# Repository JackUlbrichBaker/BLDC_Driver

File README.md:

BLDC Driver Board based on the STM32G4 Embedded motor driver:

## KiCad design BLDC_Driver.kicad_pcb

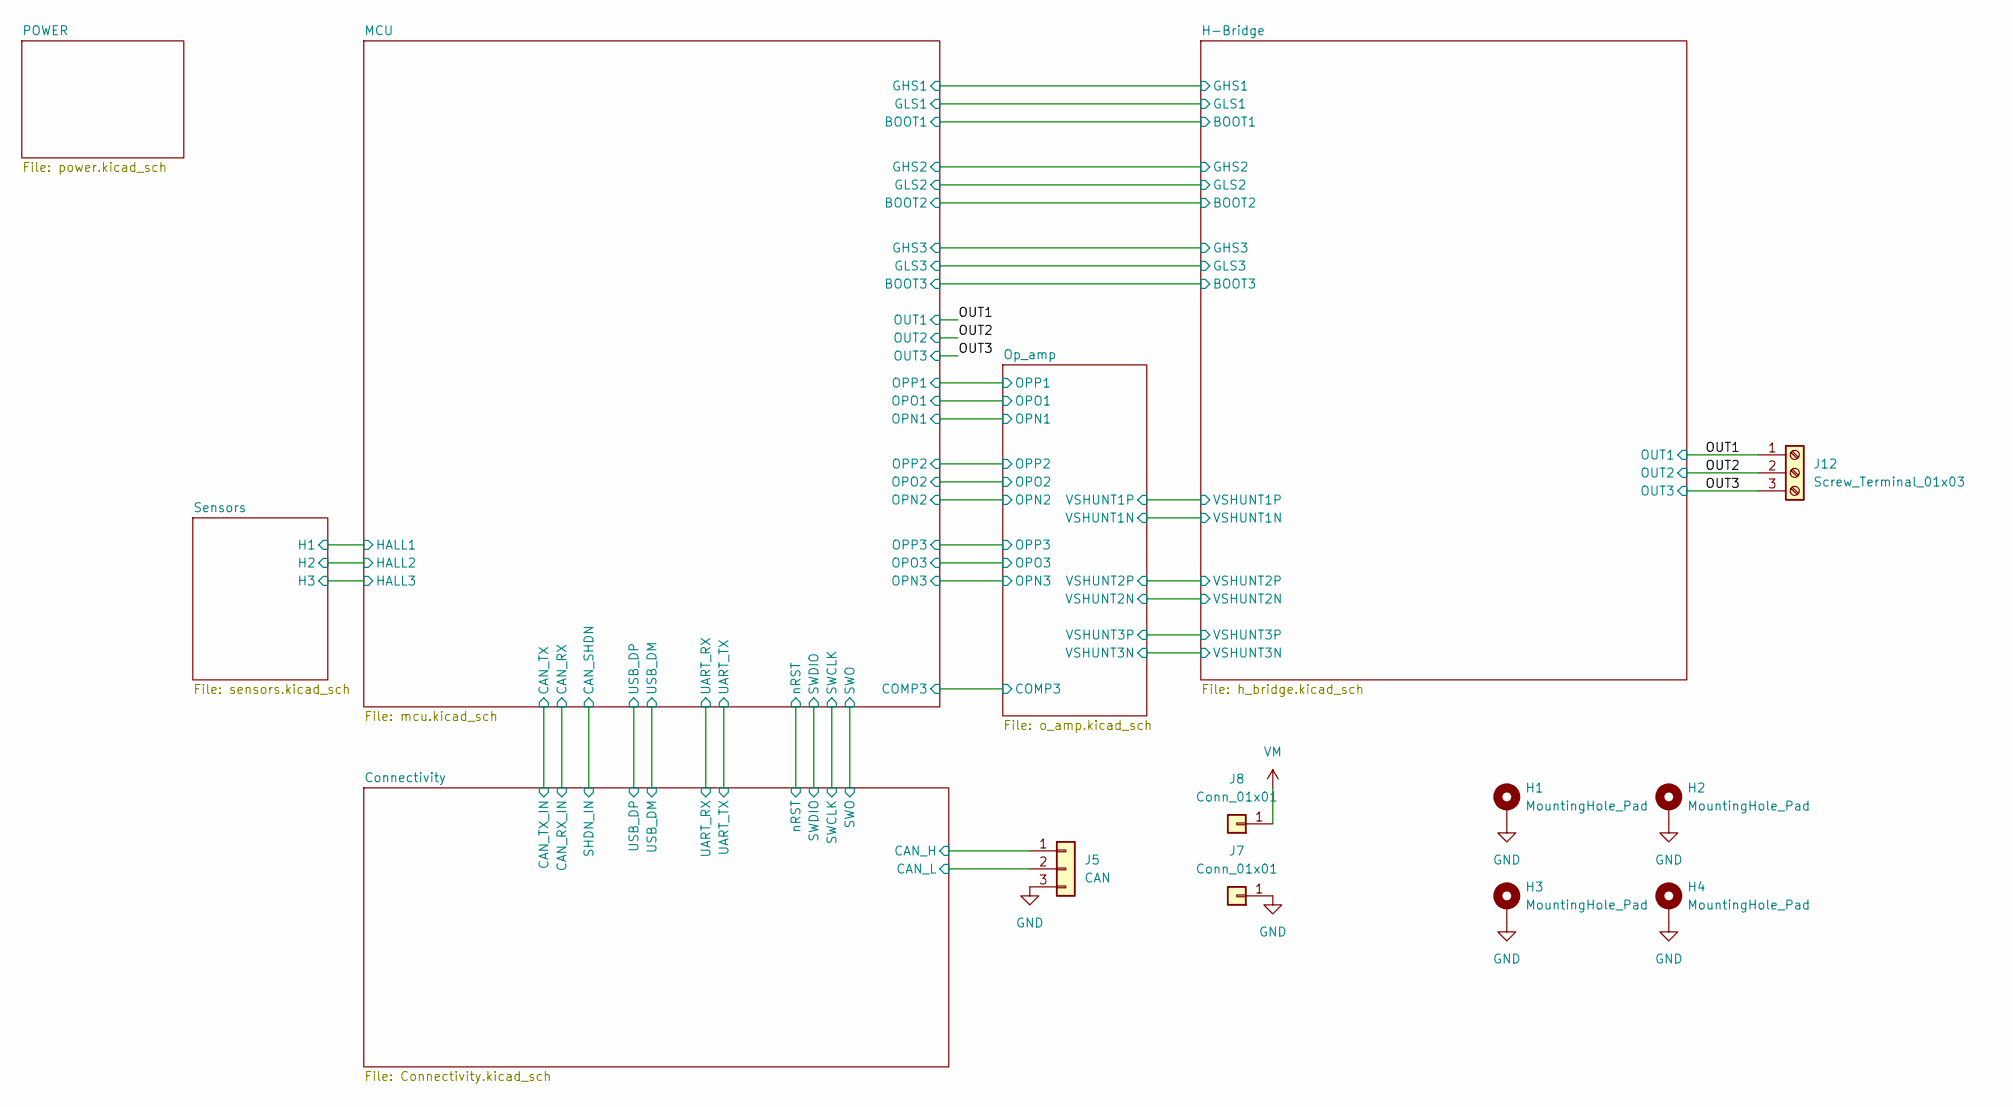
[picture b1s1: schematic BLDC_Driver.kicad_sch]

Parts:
H1, H2, H3, H4: MountingHole_Pad; MountingHole_3.2mm_M3_Pad_Via
J5: CAN; PinSocket_1x03_P2.54mm_Vertical; Part Number 1-0301FBV0T
J7, J8: Conn_01x01; SolderWire-2sqmm_1x01_D2mm_OD3.9mm
J12: Screw_Terminal_01x03; TerminalBlock_RND_205-00068_1x03_P7.50mm_Horizontal

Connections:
/OUT1: J12.1; also elsewhere on the board
/OUT2: J12.2; also elsewhere on the board
/OUT3: J12.3; also elsewhere on the board
CAN_H: J5.1; also elsewhere on the board
CAN_L: J5.2; also elsewhere on the board
GND: H1.1, H2.1, H3.1, H4.1, J5.3, J7.1; also elsewhere on the board
VM: J8.1; also elsewhere on the board

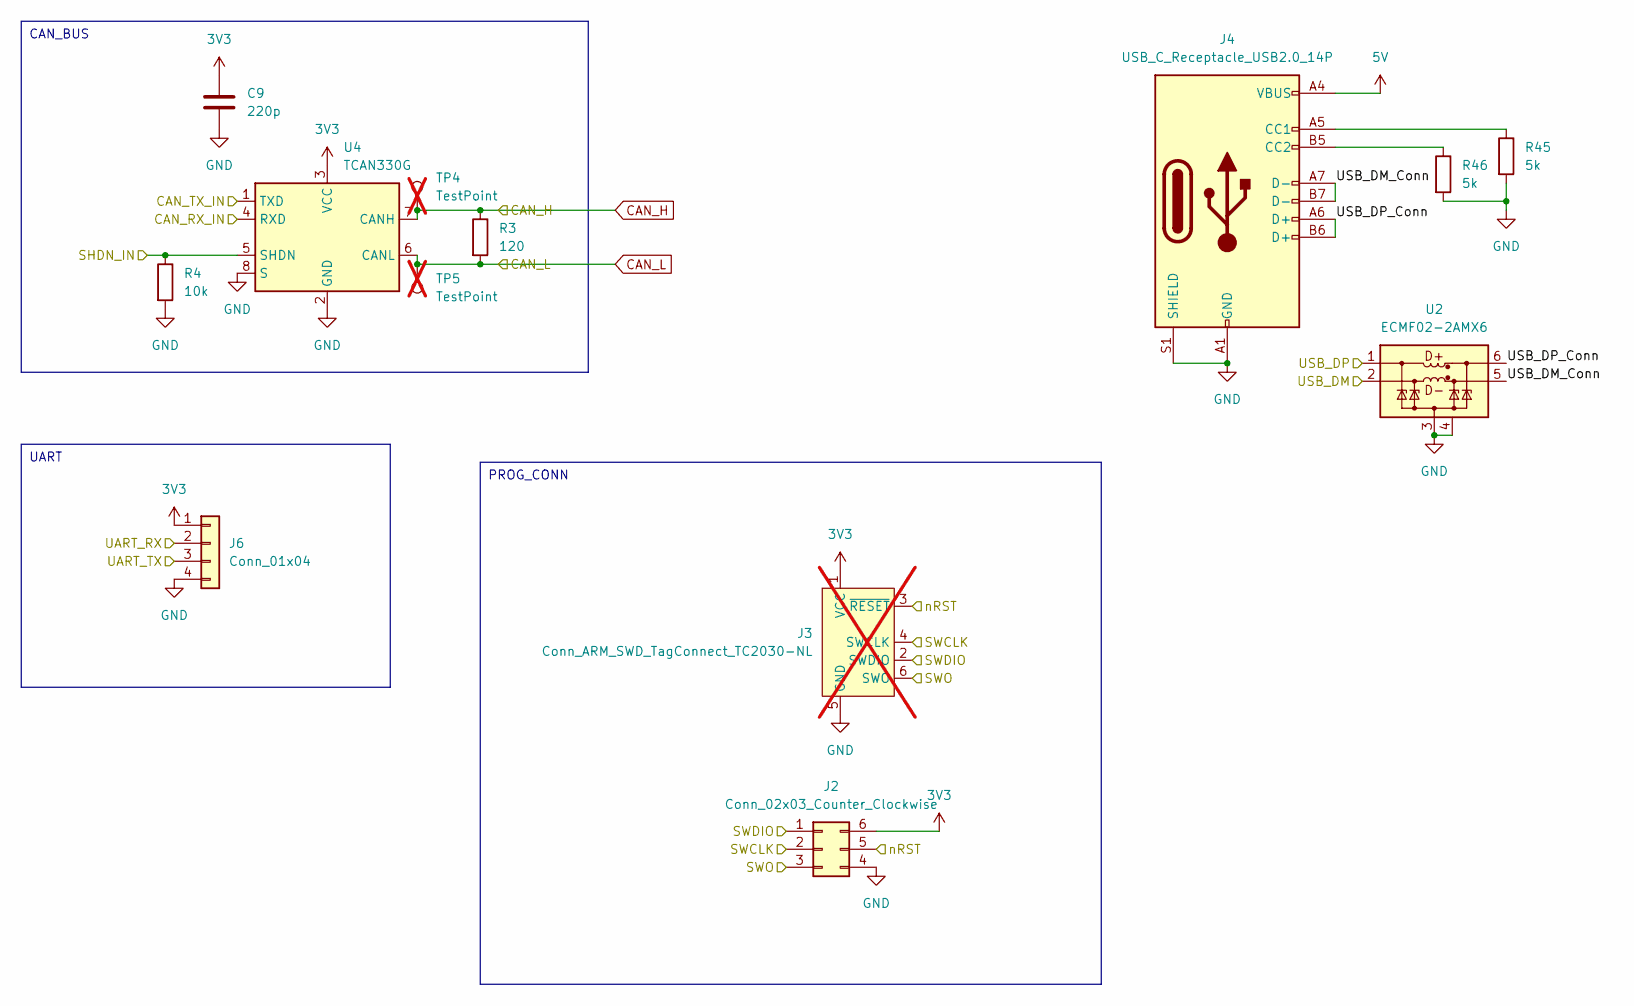
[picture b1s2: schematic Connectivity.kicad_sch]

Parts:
C9: 220p; C_0603_1608Metric_Pad1.08x0.95mm_HandSolder
J2: Conn_02x03_Counter_Clockwise; PinSocket_2x03_P2.54mm_Vertical_SMD
J3: Conn_ARM_SWD_TagConnect_TC2030-NL; Tag-Connect_TC2030-IDC-NL_2x03_P1.27mm_Vertical; not fitted
J4: USB_C_Receptacle_USB2.0_14P; USB_C_Receptacle_Amphenol_12401610E4-2A_CircularHoles
J6: Conn_01x04; PinHeader_1x04_P2.54mm_Vertical_SMD_Pin1Left
R3: 120; R_0603_1608Metric
R4: 10k; R_0603_1608Metric
R45, R46: 5k; R_0603_1608Metric
TP4, TP5: TestPoint; TestPoint_Pad_2.0x2.0mm; not fitted
U2: ECMF02-2AMX6; ST_UQFN-6L_1.5x1.7mm_P0.5mm
U4: TCAN330G; SOIC-8_3.9x4.9mm_P1.27mm

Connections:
3V3: C9.1, J2.6, J3.1 (VCC), J6.1, U4.3 (VCC); also elsewhere on the board
5V: J4.A4 (VBUS), J4.A9 (VBUS), J4.B4 (VBUS), J4.B9 (VBUS); also elsewhere on the board
/Connectivity/CAN_RX_IN: U4.4 (RXD); also elsewhere on the board
/Connectivity/CAN_TX_IN: U4.1 (TXD); also elsewhere on the board
/Connectivity/SHDN_IN: R4.1, U4.5 (SHDN); also elsewhere on the board
/Connectivity/SWCLK: J2.2, J3.4 (SWCLK); also elsewhere on the board
/Connectivity/SWDIO: J2.1, J3.2 (SWDIO); also elsewhere on the board
/Connectivity/SWO: J2.3, J3.6 (SWO); also elsewhere on the board
/Connectivity/UART_RX: J6.2; also elsewhere on the board
/Connectivity/UART_TX: J6.3; also elsewhere on the board
/Connectivity/USB_DM: U2.2 (D-_in); also elsewhere on the board
/Connectivity/USB_DM_Conn: J4.A7 (D-), J4.B7 (D-), U2.5 (D-_out)
/Connectivity/USB_DP: U2.1 (D+_in); also elsewhere on the board
/Connectivity/USB_DP_Conn: J4.A6 (D+), J4.B6 (D+), U2.6 (D+_out)
/Connectivity/nRST: J2.5, J3.3 (~RESET); also elsewhere on the board
CAN_H: R3.1, TP4.1, U4.7 (CANH); also elsewhere on the board
CAN_L: R3.2, TP5.1, U4.6 (CANL); also elsewhere on the board
GND: C9.2, J2.4, J3.5 (GND), J4.A1 (GND), J4.A12 (GND), J4.B1 (GND), J4.B12 (GND), J4.S1 (SHIELD), J6.4, R4.2, R45.2, R46.2, U2.3 (GND), U2.4 (NC), U4.2 (GND), U4.8 (S); also elsewhere on the board
unnamed: J4.A5 (CC1), R45.1
unnamed: J4.B5 (CC2), R46.1

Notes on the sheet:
UART
CAN_BUS
PROG_CONN

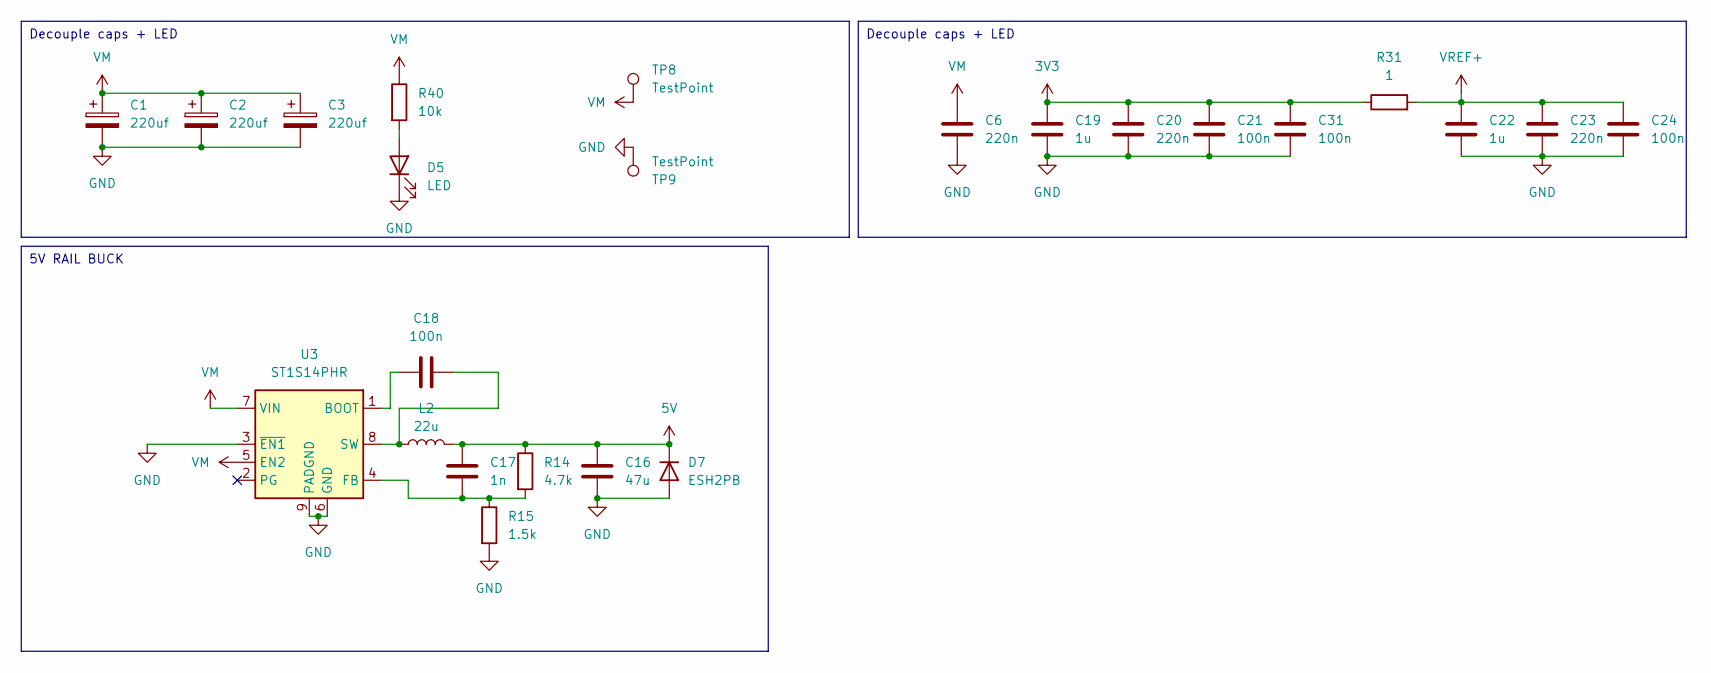
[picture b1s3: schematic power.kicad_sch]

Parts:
C1, C2, C3: 220uf; C_Elec_6.3x7.7
C6, C20, C23: 220n; C_0603_1608Metric_Pad1.08x0.95mm_HandSolder
C16: 47u; C_0603_1608Metric_Pad1.08x0.95mm_HandSolder
C17: 1n; C_0603_1608Metric_Pad1.08x0.95mm_HandSolder
C18, C21, C24, C31: 100n; C_0603_1608Metric_Pad1.08x0.95mm_HandSolder
C19, C22: 1u; C_0603_1608Metric_Pad1.08x0.95mm_HandSolder
D5: LED; D_0603_1608Metric_Pad1.05x0.95mm_HandSolder
D7: ESH2PB; D_SMP_DO-220AA
L2: 22u; L_Wurth_WE-LQSH-4020
R14: 4.7k; R_0603_1608Metric
R15: 1.5k; R_0603_1608Metric
R31: 1; R_0603_1608Metric
R40: 10k; R_0603_1608Metric
TP8, TP9: TestPoint; TestPoint_Pad_2.0x2.0mm
U3: ST1S14PHR; TI_SO-PowerPAD-8

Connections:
3V3: C19.1, C20.1, C21.1, C31.1, R31.1; also elsewhere on the board
5V: C16.1, C17.1, D7.1 (K), L2.2, R14.1; also elsewhere on the board
GND: C1.2, C2.2, C3.2, C6.2, C16.2, C19.2, C20.2, C21.2, C22.2, C23.2, C24.2, C31.2, D5.1 (K), D7.2 (A), R15.2, TP9.1, U3.3 (~EN1), U3.6 (GND), U3.9 (PADGND); also elsewhere on the board
unnamed: D5.2 (A), R40.2
unnamed: C18.1, U3.1 (BOOT)
unnamed: C17.2, R14.2, R15.1, U3.4 (FB)
unnamed: C18.2, L2.1, U3.8 (SW)
VM: C1.1, C2.1, C3.1, C6.1, R40.1, TP8.1, U3.5 (EN2), U3.7 (VIN); also elsewhere on the board
VREF+: C22.1, C23.1, C24.1, R31.2; also elsewhere on the board

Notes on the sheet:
Decouple caps + LED
5V RAIL BUCK

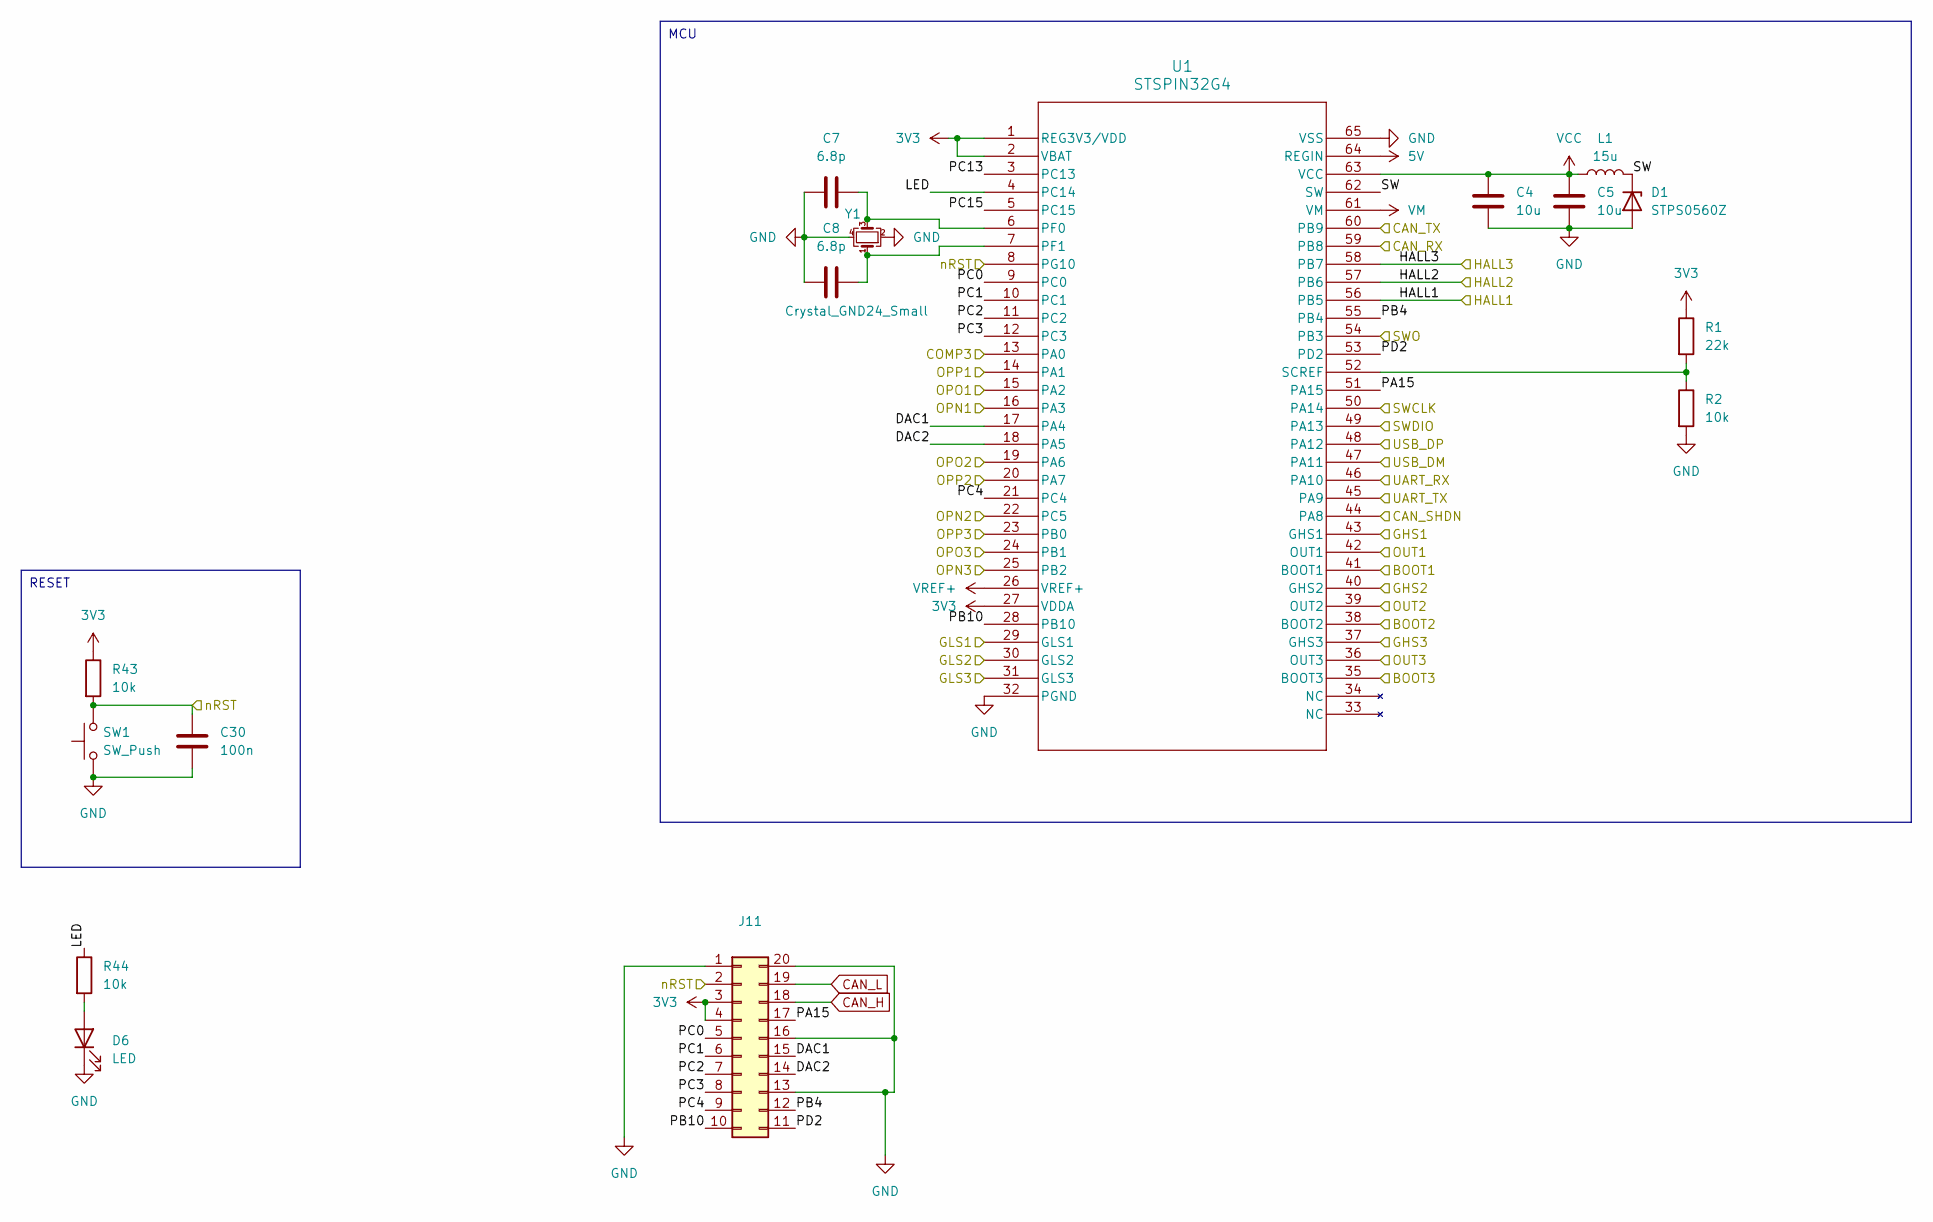
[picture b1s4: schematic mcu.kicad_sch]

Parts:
C4, C5: 10u; C_0603_1608Metric_Pad1.08x0.95mm_HandSolder
C7, C8: 6.8p; C_0603_1608Metric_Pad1.08x0.95mm_HandSolder
C30: 100n; C_0603_1608Metric_Pad1.08x0.95mm_HandSolder
D1: STPS0560Z; D_SOD-123
D6: LED; D_0603_1608Metric_Pad1.05x0.95mm_HandSolder
J11: Conn_02x10_Counter_Clockwise; Molex_Micro-Fit_3.0_43045-2021_2x10-1MP_P3.00mm_Horizontal
L1: 15u; L_Wurth_WE-LQSH-2512
R1: 22k; R_0603_1608Metric
R2, R43, R44: 10k; R_0603_1608Metric
SW1: SW_Push; SW_SPST_CK_RS282G05A3
U1: STSPIN32G4; QFN-64-1EP_9x9mm_P0.5mm_EP4.1x4.1mm_ThermalVias
Y1: Crystal_GND24_Small; Crystal_SMD_Abracon_ABM8G-4Pin_3.2x2.5mm

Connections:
3V3: J11.3, J11.4, R1.1, R43.1, U1.1 (REG3V3/VDD), U1.2 (VBAT), U1.27 (VDDA); also elsewhere on the board
5V: U1.64 (REGIN); also elsewhere on the board
/Connectivity/CAN_RX_IN: U1.59 (PB8); also elsewhere on the board
/Connectivity/CAN_TX_IN: U1.60 (PB9); also elsewhere on the board
/Connectivity/SHDN_IN: U1.44 (PA8); also elsewhere on the board
/Connectivity/SWCLK: U1.50 (PA14); also elsewhere on the board
/Connectivity/SWDIO: U1.49 (PA13); also elsewhere on the board
/Connectivity/SWO: U1.54 (PB3); also elsewhere on the board
/Connectivity/UART_RX: U1.46 (PA10); also elsewhere on the board
/Connectivity/UART_TX: U1.45 (PA9); also elsewhere on the board
/Connectivity/USB_DM: U1.47 (PA11); also elsewhere on the board
/Connectivity/USB_DP: U1.48 (PA12); also elsewhere on the board
/Connectivity/nRST: C30.1, J11.2, R43.2, SW1.2, U1.8 (PG10); also elsewhere on the board
/H-Bridge/BOOT1: U1.41 (BOOT1); also elsewhere on the board
/H-Bridge/BOOT2: U1.38 (BOOT2); also elsewhere on the board
/H-Bridge/BOOT3: U1.35 (BOOT3); also elsewhere on the board
/H-Bridge/GHS1: U1.43 (GHS1); also elsewhere on the board
/H-Bridge/GHS2: U1.40 (GHS2); also elsewhere on the board
/H-Bridge/GHS3: U1.37 (GHS3); also elsewhere on the board
/H-Bridge/GLS1: U1.29 (GLS1); also elsewhere on the board
/H-Bridge/GLS2: U1.30 (GLS2); also elsewhere on the board
/H-Bridge/GLS3: U1.31 (GLS3); also elsewhere on the board
/MCU/COMP3: U1.13 (PA0); also elsewhere on the board
/MCU/DAC1: J11.15, U1.17 (PA4)
/MCU/DAC2: J11.14, U1.18 (PA5)
/MCU/HALL1: U1.56 (PB5); also elsewhere on the board
/MCU/HALL2: U1.57 (PB6); also elsewhere on the board
/MCU/HALL3: U1.58 (PB7); also elsewhere on the board
/MCU/LED: R44.1, U1.4 (PC14)
/MCU/OPN1: U1.16 (PA3); also elsewhere on the board
/MCU/OPN2: U1.22 (PC5); also elsewhere on the board
/MCU/OPN3: U1.25 (PB2); also elsewhere on the board
/MCU/OPO1: U1.15 (PA2); also elsewhere on the board
/MCU/OPO2: U1.19 (PA6); also elsewhere on the board
/MCU/OPO3: U1.24 (PB1); also elsewhere on the board
/MCU/OPP1: U1.14 (PA1); also elsewhere on the board
/MCU/OPP2: U1.20 (PA7); also elsewhere on the board
/MCU/OPP3: U1.23 (PB0); also elsewhere on the board
/MCU/PA15: J11.17, U1.51 (PA15)
/MCU/PB4: J11.12, U1.55 (PB4)
/MCU/PB10: J11.10, U1.28 (PB10)
/MCU/PC0: J11.5, U1.9 (PC0)
/MCU/PC1: J11.6, U1.10 (PC1)
/MCU/PC2: J11.7, U1.11 (PC2)
/MCU/PC3: J11.8, U1.12 (PC3)
/MCU/PC4: J11.9, U1.21 (PC4)
/MCU/PC13: U1.3 (PC13)
/MCU/PC15: U1.5 (PC15)
/MCU/PD2: J11.11, U1.53 (PD2)
/MCU/SW: D1.1 (K), L1.2, U1.62 (SW)
/OUT1: U1.42 (OUT1); also elsewhere on the board
/OUT2: U1.39 (OUT2); also elsewhere on the board
/OUT3: U1.36 (OUT3); also elsewhere on the board
CAN_H: J11.18; also elsewhere on the board
CAN_L: J11.19; also elsewhere on the board
GND: C4.2, C5.2, C7.1, C8.2, C30.2, D1.2 (A), D6.1 (K), J11.1, J11.13, J11.16, J11.20, R2.2, SW1.1, U1.32 (PGND), U1.65 (VSS), Y1.2, Y1.4; also elsewhere on the board
unnamed: D6.2 (A), R44.2
unnamed: C7.2, U1.6 (PF0), Y1.3
unnamed: C8.1, U1.7 (PF1), Y1.1
unnamed: R1.2, R2.1, U1.52 (SCREF)
VCC: C4.1, C5.1, L1.1, U1.63 (VCC)
VM: U1.61 (VM); also elsewhere on the board
VREF+: U1.26 (VREF+); also elsewhere on the board

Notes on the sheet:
MCU
RESET

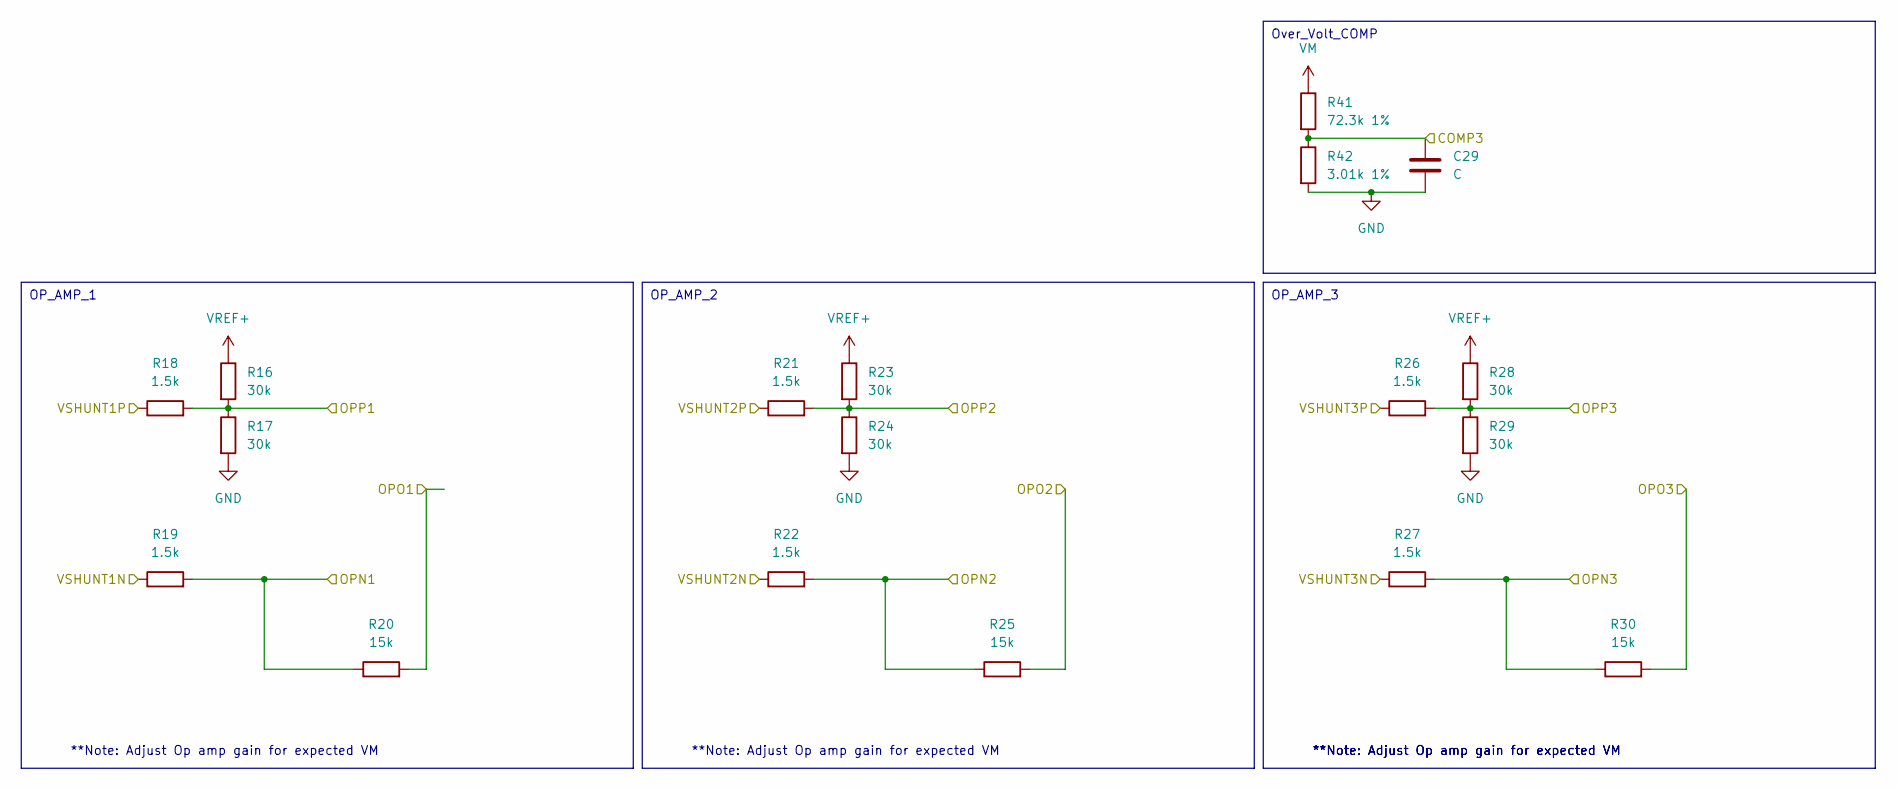
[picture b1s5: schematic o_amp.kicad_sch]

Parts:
C29: C; C_0603_1608Metric_Pad1.08x0.95mm_HandSolder
R16, R17, R23, R24, R28, R29: 30k; R_0603_1608Metric
R18, R19, R21, R22, R26, R27: 1.5k; R_0603_1608Metric
R20, R25, R30: 15k; R_0603_1608Metric
R41: 72.3k 1%; R_0603_1608Metric
R42: 3.01k 1%; R_0603_1608Metric

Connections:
/H-Bridge/VSHUNT1P: R18.1; also elsewhere on the board
/H-Bridge/VSHUNT2P: R21.1; also elsewhere on the board
/H-Bridge/VSHUNT3P: R26.1; also elsewhere on the board
/MCU/COMP3: C29.1, R41.2, R42.1; also elsewhere on the board
/MCU/OPN1: R19.2, R20.1; also elsewhere on the board
/MCU/OPN2: R22.2, R25.1; also elsewhere on the board
/MCU/OPN3: R27.2, R30.1; also elsewhere on the board
/MCU/OPO1: R20.2; also elsewhere on the board
/MCU/OPO2: R25.2; also elsewhere on the board
/MCU/OPO3: R30.2; also elsewhere on the board
/MCU/OPP1: R16.2, R17.1, R18.2; also elsewhere on the board
/MCU/OPP2: R21.2, R23.2, R24.1; also elsewhere on the board
/MCU/OPP3: R26.2, R28.2, R29.1; also elsewhere on the board
GND: C29.2, R17.2, R19.1, R22.1, R24.2, R27.1, R29.2, R42.2; also elsewhere on the board
VM: R41.1; also elsewhere on the board
VREF+: R16.1, R23.1, R28.1; also elsewhere on the board

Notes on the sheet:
OP_AMP_2
OP_AMP_1
Over_Volt_COMP
OP_AMP_3
**Note: Adjust Op amp gain for expected VM

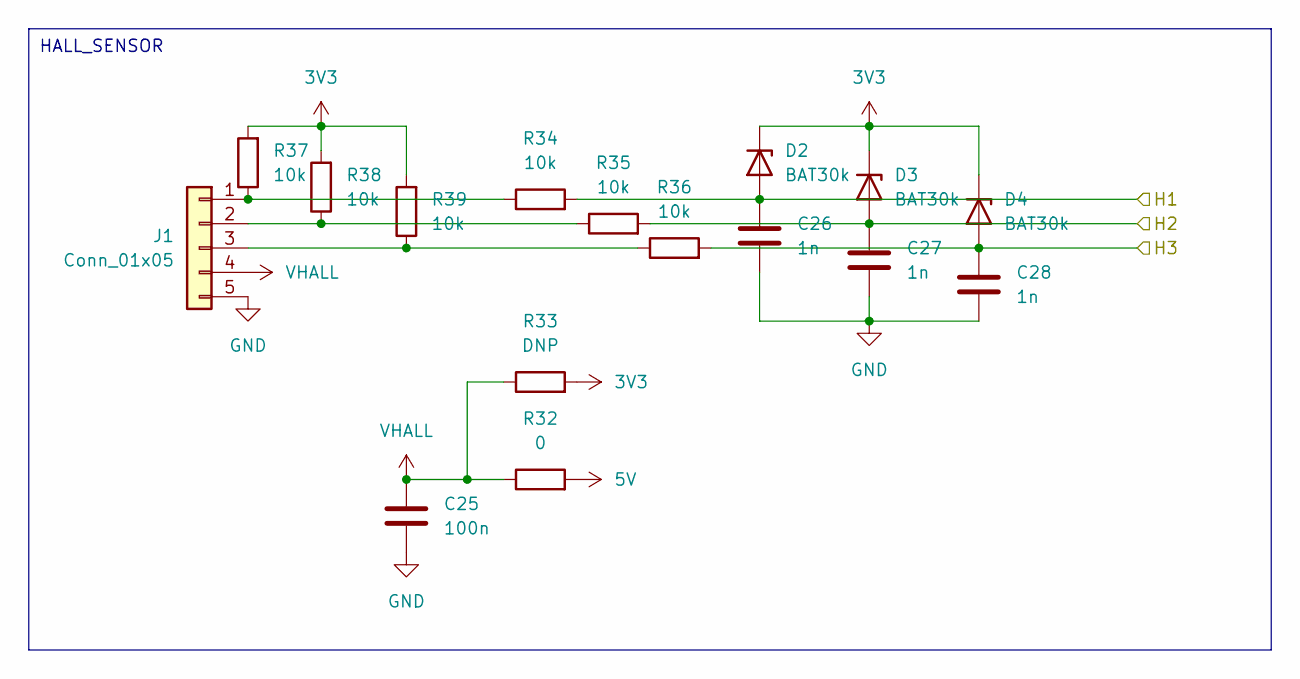
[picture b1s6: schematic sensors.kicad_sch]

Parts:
C25: 100n; C_0603_1608Metric_Pad1.08x0.95mm_HandSolder
C26, C27, C28: 1n; C_0603_1608Metric_Pad1.08x0.95mm_HandSolder
D2, D3, D4: BAT30k; D_SOD-523
J1: Conn_01x05; PinSocket_1x05_P2.54mm_Vertical
R32: 0; R_0603_1608Metric
R33: DNP; R_0603_1608Metric
R34, R35, R36, R37, R38, R39: 10k; R_0603_1608Metric

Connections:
3V3: D2.1 (K), D3.1 (K), D4.1 (K), R33.2, R37.2, R38.2, R39.2; also elsewhere on the board
5V: R32.2; also elsewhere on the board
/MCU/HALL1: C26.1, D2.2 (A), R34.2; also elsewhere on the board
/MCU/HALL2: C27.1, D3.2 (A), R35.2; also elsewhere on the board
/MCU/HALL3: C28.1, D4.2 (A), R36.2; also elsewhere on the board
GND: C25.2, C26.2, C27.2, C28.2, J1.5; also elsewhere on the board
unnamed: J1.1, R34.1, R37.1
unnamed: J1.2, R35.1, R38.1
unnamed: J1.3, R36.1, R39.1
VHALL: C25.1, J1.4, R32.1, R33.1

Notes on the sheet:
HALL_SENSOR

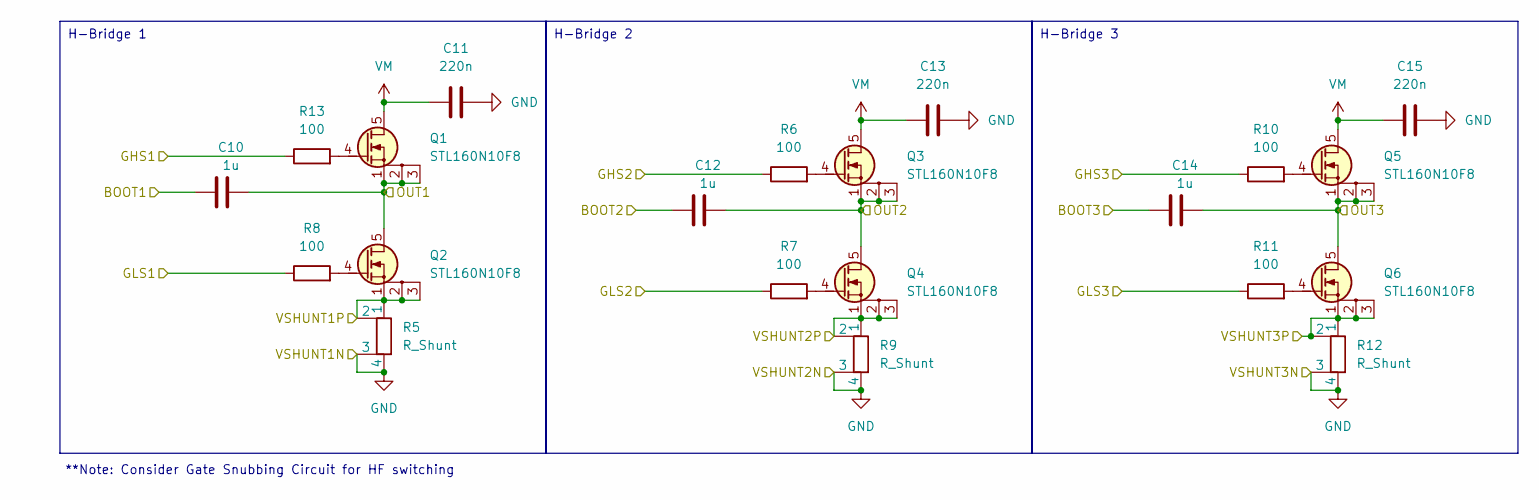
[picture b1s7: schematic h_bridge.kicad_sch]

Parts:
C10, C12, C14: 1u; C_0603_1608Metric_Pad1.08x0.95mm_HandSolder
C11, C13, C15: 220n; C_0603_1608Metric_Pad1.08x0.95mm_HandSolder
Q1, Q2, Q3, Q4, Q5, Q6: STL160N10F8; Infineon_PG-TDSON-8
R5, R9, R12: R_Shunt; R_Shunt_Vishay_WSK2512_6332Metric_T2.66mm
R6, R7, R8, R10, R11, R13: 100; R_0603_1608Metric

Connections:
/H-Bridge/BOOT1: C10.1; also elsewhere on the board
/H-Bridge/BOOT2: C12.1; also elsewhere on the board
/H-Bridge/BOOT3: C14.1; also elsewhere on the board
/H-Bridge/GHS1: R13.1; also elsewhere on the board
/H-Bridge/GHS2: R6.1; also elsewhere on the board
/H-Bridge/GHS3: R10.1; also elsewhere on the board
/H-Bridge/GLS1: R8.1; also elsewhere on the board
/H-Bridge/GLS2: R7.1; also elsewhere on the board
/H-Bridge/GLS3: R11.1; also elsewhere on the board
/H-Bridge/VSHUNT1P: Q2.1 (S), Q2.2 (S), Q2.3 (S), R5.1, R5.2; also elsewhere on the board
/H-Bridge/VSHUNT2P: Q4.1 (S), Q4.2 (S), Q4.3 (S), R9.1, R9.2; also elsewhere on the board
/H-Bridge/VSHUNT3P: Q6.1 (S), Q6.2 (S), Q6.3 (S), R12.1, R12.2; also elsewhere on the board
/OUT1: C10.2, Q1.1 (S), Q1.2 (S), Q1.3 (S), Q2.5 (D); also elsewhere on the board
/OUT2: C12.2, Q3.1 (S), Q3.2 (S), Q3.3 (S), Q4.5 (D); also elsewhere on the board
/OUT3: C14.2, Q5.1 (S), Q5.2 (S), Q5.3 (S), Q6.5 (D); also elsewhere on the board
GND: C11.2, C13.2, C15.2, R5.3, R5.4, R9.3, R9.4, R12.3, R12.4; also elsewhere on the board
unnamed: Q1.4 (G), R13.2
unnamed: Q2.4 (G), R8.2
unnamed: Q3.4 (G), R6.2
unnamed: Q4.4 (G), R7.2
unnamed: Q5.4 (G), R10.2
unnamed: Q6.4 (G), R11.2
VM: C11.1, C13.1, C15.1, Q1.5 (D), Q3.5 (D), Q5.5 (D); also elsewhere on the board

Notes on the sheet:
H-Bridge 3
H-Bridge 2
H-Bridge 1
**Note: Consider Gate Snubbing Circuit for HF switching

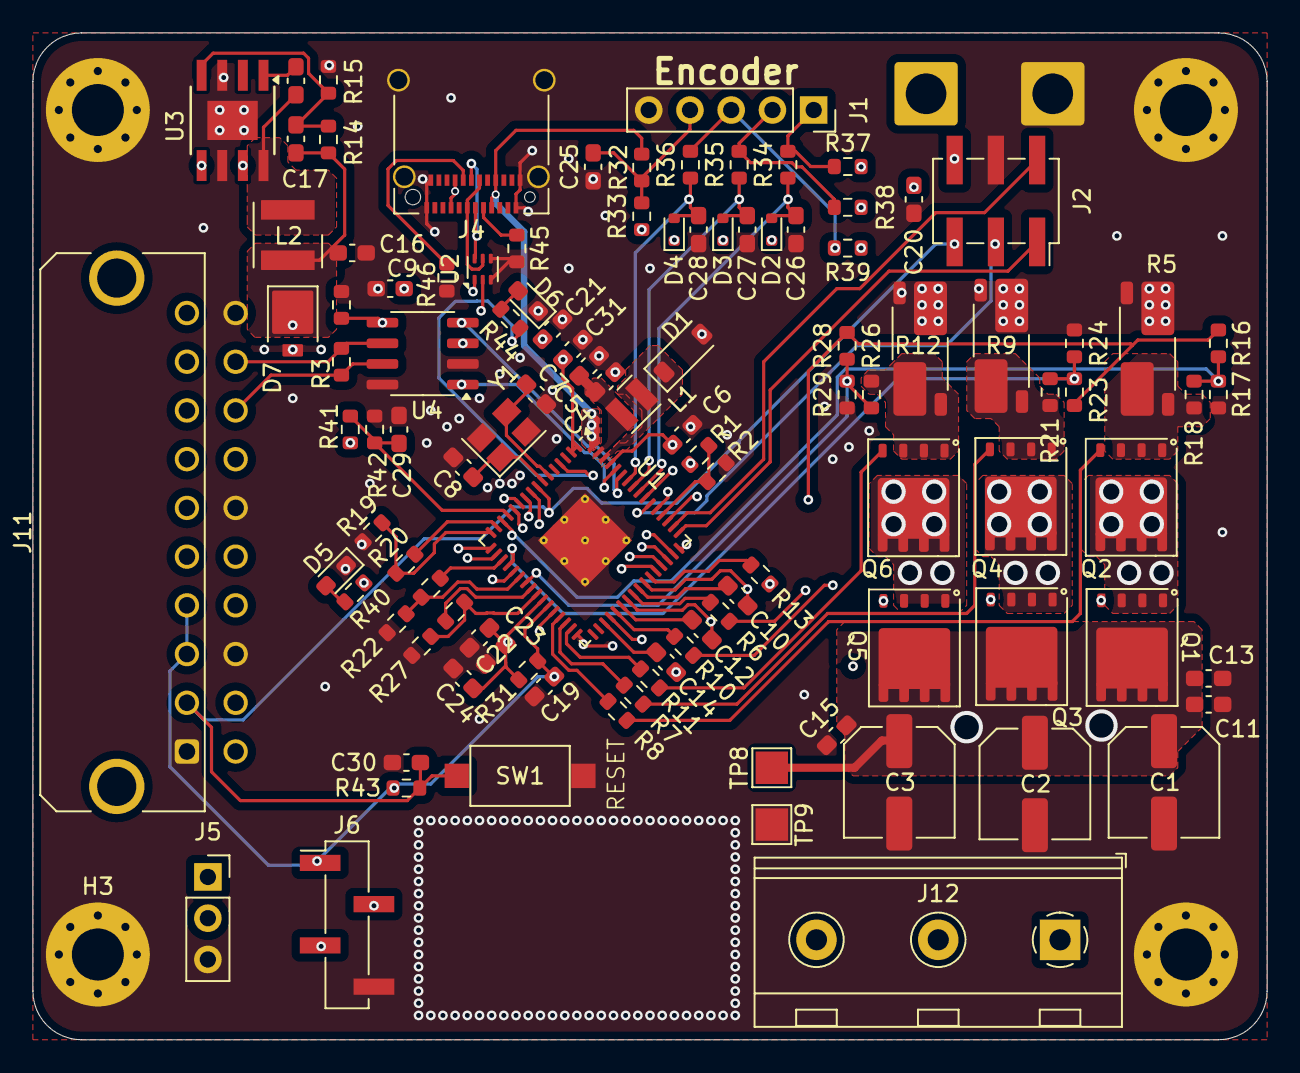
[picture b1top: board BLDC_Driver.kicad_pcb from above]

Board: 6 copper layers, 76.0 x 62.0 mm, 113 parts (0 on the bottom side), 82 nets.

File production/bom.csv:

Designator,Footprint,Quantity,Value,LCSC Part #
"C1, C2, C3",C_Elec_6.3x7.7,3,220uf,
"C10, C12, C14, C19, C22",0603,5,1u,
"C11, C13, C15, C20, C23, C6",0603,6,220n,
C16,0603,1,47u,
"C17, C26, C27, C28",0603,4,1n,
"C18, C21, C24, C25, C30, C31",0603,6,100n,
C29,0603,1,C,
"C4, C5",0603,2,10u,
"C7, C8",0603,2,6.8p,
C9,0603,1,220p,
D1,D_SOD-123,1,STPS0560Z,
"D2, D3, D4",D_SOD-523,3,BAT30k,
"D5, D6",0603,2,LED,
D7,D_SMP_DO-220AA,1,ESH2PB,
J1,PinSocket_1x05_P2.54mm_Vertical,1,Conn_01x05,
J11,Molex_Micro-Fit_3.0_43045-2021_2x10-1MP_P3.00mm_Horizontal,1,Conn_02x10_Counter_Clockwise,
J12,TerminalBlock_RND_205-00068_1x03_P7.50mm_Horizontal,1,Screw_Terminal_01x03,
J2,PinSocket_2x03_P2.54mm_Vertical_SMD,1,Conn_02x03_Counter_Clockwise,
J4,USB_C_Receptacle_Amphenol_12401610E4-2A_CircularHoles,1,USB_C_Receptacle_USB2.0_14P,
J5,PinSocket_1x03_P2.54mm_Vertical,1,CAN,
J6,PinHeader_1x04_P2.54mm_Vertical_SMD_Pin1Left,1,Conn_01x04,
"J7, J8",SolderWire-2sqmm_1x01_D2mm_OD3.9mm,2,Conn_01x01,
L1,L_Wurth_WE-LQSH-2512,1,15u,
L2,L_Wurth_WE-LQSH-4020,1,22u,
"Q1, Q2, Q3, Q4, Q5, Q6",Infineon_PG-TDSON-8,6,STL160N10F8,
R1,0603,1,22k,
"R10, R11, R13, R6, R7, R8",0603,6,100,
"R12, R5, R9",R_Shunt_Vishay_WSK2512_6332Metric_T2.66mm,3,R_Shunt,
R14,0603,1,4.7k,
"R15, R18, R19, R21, R22, R26, R27",0603,7,1.5k,
"R16, R17, R23, R24, R28, R29",0603,6,30k,
"R2, R34, R35, R36, R37, R38, R39, R4, R40, R43, R44",0603,11,10k,
"R20, R25, R30",0603,3,15k,
R3,0603,1,120,
R31,0603,1,1,
R32,0603,1,0,
R41,0603,1,72.3k 1%,
R42,0603,1,3.01k 1%,
"R45, R46",0603,2,5k,
SW1,SW_SPST_CK_RS282G05A3,1,SW_Push,
"TP8, TP9",TestPoint_Pad_2.0x2.0mm,2,TestPoint,
U1,QFN-64-1EP_9x9mm_P0.5mm_EP4.1x4.1mm_ThermalVias,1,STSPIN32G4,
U2,ST_UQFN-6L_1.5x1.7mm_P0.5mm,1,ECMF02-2AMX6,
U3,TI_SO-PowerPAD-8,1,ST1S14PHR,
U4,SOIC-8_3.9x4.9mm_P1.27mm,1,TCAN330G,
Y1,Crystal_SMD_Abracon_ABM8G-4Pin_3.2x2.5mm,1,Crystal_GND24_Small,

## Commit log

2025-05-10 init
2025-06-11 layout
2025-07-23 All DONE >?git add .git add .
2025-09-03 current changes as of production
